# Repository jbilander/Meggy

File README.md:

# Meggy
A 1MB USB-programmable Kickstart ROM board for Amiga computers with a 42-pin ROM socket (A500+, A600). With a small modification also works in machines with a 40-pin ROM socket such as the A500 rev 6A and B2000.

***

<br />

<br />

<br />

<br />

<br />

***

# Bill of Materials — Meggy Rev C

| Ref | Qty | Value | Description | Package | Notes | Mouser |
|-----|-----|-------|-------------|---------|-------|--------|
| U1 | 2 | — | Pin strip 1×21, 2.54mm pitch, 0.4mm square pins | — | <span title="Cut from 1×50 1.27mm pitch strip, remove every other pin to give 2.54mm pitch. Fits Amiga dual-wipe socket better than standard 0.47mm turned pins.">Pin strip info...</span> | [AliExpress example](https://www.aliexpress.com/item/4000979931385.html) |
| U2 | 1 | AT90USB1286-MU | AVR USB microcontroller | QFN-64 | | [556-AT90USB1286-MU](https://www.mouser.com/ProductDetail/556-AT90USB1286-MU) |
| U3 | 1 | M29F160FT55N3E2 | 2MB NOR Flash (top-boot) | TSOP-48 | | [913-M29F160FT55N3E2](https://www.mouser.com/ProductDetail/913-M29F160FT55N3E2) |
| U4 | 1 | 74AHCT1G126GW | Single tristate buffer | SC-70-5 / SOT-353 | <span title="Isolates Gary's /OE signal from the flash chip during USB programming. 10k pull-up on EN keeps buffer enabled by default even with no firmware loaded.">OE isolation...</span> | [771-AHCT1G126GW125](https://www.mouser.com/ProductDetail/771-AHCT1G126GW125) |
| D1, D2 | 2 | CDBU0520 | Schottky diode 0.5A 20V | SOD-523F / 0603 | <span title="Diode-OR between VBUS (USB 5V) and VCC (Amiga 5V). Prevents backfeed between the two supplies. Higher voltage wins.">Power OR...</span> | [750-CDBU0520](https://www.mouser.com/ProductDetail/750-CDBU0520) |
| X1 | 1 | 16 MHz | Crystal oscillator SG5032CCN 16.000000M-HJGA3 | 5×3.2mm SMD | | [732-5032CC16.0HJGA3](https://www.mouser.com/ProductDetail/732-5032CC16.0HJGA3) |
| SW1 | 1 | — | Sunrom Tactile Switch SMD | 3×4×2mm | <span title="Hold HWB button and run --avr-reset to enter DFU bootloader mode for firmware programming.">HWB / DFU entry...</span> | [AliExpress example](https://www.aliexpress.com/item/32855171871.html) |
| J1 | 1 | 10118194-0001LF | Micro USB-B connector, Amphenol FCI, 5-pin | SMD | | [649-10118194-0001LF](https://www.mouser.com/ProductDetail/649-10118194-0001LF) |
| J2 | 1 | MSK12D19 SMD | SMD slide switch, 3-pin, 2.5mm pitch | SMD | <span title="Flash A19 select — open = slot 1 (pull-up), shorted to GND = slot 0. Pins bent to right angle for flush mounting. Alternatively a 3-pin 2.54mm right-angle pin header with external toggle switch.">Flash A19 slot select...</span> | [AliExpress example](https://www.aliexpress.com/item/1005006482584650.html) |
| RN1, RN2 | 2 | 10k | Resistor network 4×10kΩ isolated | 0603×4 (1206) | CAY16-103J4LF | [652-CAY16-103J4LF](https://www.mouser.com/ProductDetail/652-CAY16-103J4LF) |
| R1, R2 | 2 | 22Ω | CR0603-FX-22R0ELF — USB D+/D− series resistors | 0603 | | [652-CR0603FX-22R0ELF](https://www.mouser.com/ProductDetail/652-CR0603FX-22R0ELF) |
| R3 | 1 | 22Ω | CR0603-FX-22R0ELF — Clock series termination | 0603 | | [652-CR0603FX-22R0ELF](https://www.mouser.com/ProductDetail/652-CR0603FX-22R0ELF) |
| R4 | 1 | 100Ω | CR0603-FX-1000ELF — VBUS detection | 0603 | <span title="Series resistor between VBUS_5V and AVR VBUS pin 8 for USB bus voltage detection.">VBUS detect...</span> | [652-CR0603FX-1000ELF](https://www.mouser.com/ProductDetail/652-CR0603FX-1000ELF) |
| R5 | 1 | 10kΩ | CR0603-FX-1002ELF — OE_BUF_EN pull-up | 0603 | <span title="Pull-up to VCC on PE4 (OE_BUF_EN). Keeps the 74AHCT1G126GW buffer enabled by default so Gary controls /OE even with no firmware loaded.">OE_BUF_EN pull-up...</span> | [652-CR0603FX-1002ELF](https://www.mouser.com/ProductDetail/652-CR0603FX-1002ELF) |
| C1 | 1 | 1µF | CL10B105KA8NNND | 0603 | <span title="UCAP filter capacitor on AVR pin 7. Required for the AT90USB1286 internal USB voltage regulator.">UCAP filter...</span> | [187-CL10B105KA8NNND](https://www.mouser.com/ProductDetail/187-CL10B105KA8NNND) |
| C2, C3, C4, C5 | 4 | 100nF | CL10B104KA8NNNC — Bypass decoupling | 0603 | <span title="Bypass decoupling capacitors. Place as close as possible to the VCC pins of U2, U3 and U4.">Bypass decoupling...</span> | [187-CL10B104KA8NNNC](https://www.mouser.com/ProductDetail/187-CL10B104KA8NNNC) |

## Key ICs

**AT90USB1286-MU** — Atmel/Microchip AVR, 128KB flash, native full-speed USB, QFN-64. Runs the Meggy firmware and provides USB bulk transfer for flash programming. DFU bootloader in hardware boot section (no external programmer needed after initial setup).

**M29F160FT55N3E2** — Micron/ST 16Mbit (2MB) NOR flash, top-boot, 55ns, 5V, x16. Stores two 1MB Kickstart image slots selectable via the A19 switch. [Datasheet](https://www.mouser.com/datasheet/3/893/1/M29FxxFT_FB.pdf)

**74AHCT1G126GW** — Single buffer with tristate output (active-high enable). Isolates Gary's /OE signal from the flash chip during USB programming operations. 10k pull-up on EN ensures the buffer is enabled (Amiga in control) by default even with no firmware loaded.

**CDBU0520** — Comchip 0.5A 20V Schottky diode, SOD-523F (0603 footprint). Two used for power OR between VBUS (USB) and VCC (Amiga). Prevents backfeed between the two supplies.

## Power

The board can be powered from either:
- **VBUS** (USB 5V) — when connected to a PC for programming
- **VCC** (Amiga 5V) — when installed in the Amiga

D1 and D2 form a diode-OR, allowing both supplies to coexist safely. The higher voltage wins. Schottky forward drop is approximately 150–200mV at typical operating currents.

***

# Assembly Notes

## Pin Headers (U1)

The two 1×21 pin headers that plug into the Amiga ROM socket are made from standard **1.27 mm pitch pin strips** with every other pin used, giving 21 pins per row at 2.54 mm pitch.

The reason for starting with 1.27 mm strips rather than conventional 2.54 mm strips is pin geometry: 1.27 mm strips have **0.4 mm square pins**, which seat noticeably better in Amiga dual-wipe sockets than the turned (round) pins found on 2.54 mm strips. Turned pins are typically ~0.47 mm in diameter and can spread the socket contacts over time, whereas the slimmer square pins make clean contact without stressing the socket.

### Preparation

Start with two 1.27 mm pitch pin strips, each at least 42 pins long. Using pliers or a similar tool, push every other pin down flush with the top face of the plastic guard — these are the pins that will not be soldered. The result is a strip that alternates between full-length protruding pins and pins that sit flush inside the guard.

### Self-aligning soldering technique

Place both prepared strips on the work surface with the **plastic guard facing down** and the full-length pins pointing upward. Set the Meggy PCB flat on top so that it rests on the two strips — the full-length pins pass up through the PCB holes from below while the board's own weight holds everything in place.

Align both strips as straight as possible along the PCB edges, then **tack one corner of each strip** to hold them in position.

At this stage it is still easy to correct misalignment — reflow a tacked corner with the iron, nudge the strip with your finger, and re-tack. Check that the pins protrude consistently above the PCB along the full length of each strip before proceeding. When both strips are correctly aligned, solder all remaining pins from the top side.

After soldering, the underside of the board looks like this:

### Removing the plastic guard

With all pins soldered, grip the plastic guard firmly and pull it straight down away from the PCB. The guard separates cleanly by hand — the alternating flush pins are retained inside it and come away with it, leaving only the soldered pins.

The finished board has two neat rows of evenly spaced pins with no plastic guard to limit insertion depth, allowing Meggy to seat fully into any socket.

## J2 Slide Switch (MSK12D19) — Bending and Soldering

The MSK12D19 is an SMD slide switch soldered flat on the PCB with its pins bent over and soldered from the top side. To change the Kickstart slot the Amiga needs to be opened. Alternatively J2 can be fitted with a 3-pin 2.54mm right-angle pin header and wired to an external toggle switch mounted somewhere accessible on the Amiga case.

**Steps:**
1. Place the switch into the J2 footprint so the three pins protrude slightly through the top side of the PCB.
2. With your fingers, bend all three pins over flat against the top surface so the switch body ends up level with the board.
3. Apply flux and solder the three pins from the top side with a regular soldering iron.

## AVR Exposed Pad and USB Connector — Soldering Technique

The AT90USB1286-MU QFN-64 has a large exposed thermal pad on the underside that must be soldered to the GND pour for reliable operation. The Micro USB connector also has through-hole anchor pins. Both benefit from using a desoldering station with good thermal mass — a ZD915 or similar works well for this.

**AVR exposed pad:**
1. Apply flux into the PCB via hole that sits directly under the exposed pad.
2. Place the desoldering nozzle against the hole from the underside and feed solder wire into the nozzle, holding for 3–4 seconds. The thermal mass of the station heats the via quickly and the solder wicks up through the hole making solid contact with the exposed pad above.

**USB connector through-hole anchor pins:**
1. Apply flux on both sides of the PCB at each anchor pin hole.
2. Solder from one side — applying flux to the opposite side encourages a clean bleed-through joint, giving a solid mechanical connection.

***

# Windows Setup

Meggy uses two distinct USB personalities:

| Mode | USB ID | When active | Driver needed |
|------|--------|-------------|---------------|
| **DFU bootloader** | 03EB:2FFB | No firmware, or HWB held during power-up | libusb-win32 (via Zadig) |
| **Flash programmer** | 03EB:2044 | Normal firmware operation | WinUSB (via Zadig) |

Both drivers are installed with [Zadig](https://zadig.akeo.ie). The steps below cover the full setup from a fresh Windows machine.

## Prerequisites

- **Arduino IDE 1.8.x** — provides `avrdude.exe` used by `flash.bat` to program the AVR firmware. Tested with Arduino IDE 1.8.16. Newer versions of Arduino IDE (2.x) install avrdude in a different location and may require editing the `AVR_PATH` variable in `build.bat` and `flash.bat`. Download from [arduino.cc](https://www.arduino.cc/en/software).
- **Python 3.x** — required for `meggy_flash.py` (see Step 1 below).

---

## Step 1 — Install Python

Download Python 3.x (64-bit) from [python.org](https://www.python.org/downloads/) and run the installer.

**Important:** tick **"Add python.exe to PATH"** before clicking Install Now.

---

## Step 2 — Install PyUSB

Open a Command Prompt and run:

```
pip install pyusb
```

If you run `meggy_flash.py` before installing PyUSB you will see the reminder message shown below — just run the pip command and try again.

---

## Step 3 — Install libusb-1.0.dll

PyUSB on Windows requires `libusb-1.0.dll` to be present. Download the latest libusb release from [libusb.info](https://libusb.info), open the archive with 7-Zip or similar, and copy `libusb-1.0.dll` from the `VS2015\MS64\dll\` folder into `C:\Windows\System32`.

---

## Step 4 — Install Zadig

Download [Zadig](https://zadig.akeo.ie) (a single portable `.exe`, no installation required) and save it somewhere convenient.

---

## Step 5 — Install the DFU driver (libusb-win32)

This driver is used when Meggy is in DFU bootloader mode for **firmware** programming.

**Put Meggy into DFU mode:**

A freshly soldered board with no firmware loaded will enter DFU mode automatically on power-up — just plug in the USB cable and the device enumerates as **AT90USB128 DFU** without any button press needed.

If firmware is already installed, hold the HWB button and run `python meggy_flash.py --avr-reset` (see the Firmware Programming section below).

Windows will detect a new device. Without the driver it appears as **AT90USB128 DFU** under *Other devices* in Device Manager with a warning icon.

Open Zadig. The device **AT90USB128 DFU** (USB ID `03EB 2FFB`) should appear in the dropdown. Make sure the target driver on the right is set to **libusb-win32**, then click **Install Driver**.

Zadig installs the driver (this takes a few seconds).

When complete, Zadig reports **"The driver was installed successfully."**

Device Manager now shows **AT90USB128 DFU** under *libusb-win32 devices* — no warning icon.

---

## Step 6 — Install the Flash Programmer driver (WinUSB)

This driver is used during normal operation when Meggy presents itself as the **Meggy Flash Programmer** for **NOR flash** programming.

Unplug Meggy and plug it back in without holding HWB so it boots into normal firmware mode. Windows detects it as **Meggy Flash Programmer** under *Other devices*. If you try to install the driver via Windows Update or Device Manager directly, Windows will refuse because the INF lacks a digital signature.

Use Zadig instead. Select **Meggy Flash Programmer** (USB ID `03EB 2044`) from the dropdown and confirm the target driver on the right is **WinUSB**, then click **Install Driver**.

Zadig installs the driver and reports success.

Device Manager now shows **Meggy Flash Programmer** under *Universal Serial Bus devices*.

Both drivers are now in place and setup is complete.

***

# Firmware Programming

The AT90USB1286 ships with a USB DFU bootloader burned into the hardware boot section. This bootloader cannot be erased, so no external programmer is ever required after the chip is soldered.

## Entering DFU Mode

A freshly soldered board with no firmware loaded will enter DFU mode automatically on power-up — just plug in USB and it enumerates as **AT90USB128 DFU** (USB ID `03EB:2FFB`) without any button press needed.

If firmware is already installed:

**Preferred method** (firmware running):
1. Hold the HWB button.
2. Run `python meggy_flash.py --avr-reset`
3. Release HWB once avrdude connects.

The `--avr-reset` command triggers a hardware reset via the PE5→RESET connection, which causes the bootloader to check HWB and enter DFU mode. This is the only way to enter DFU mode when firmware is already running on Rev C.

## Building the Firmware

From the `firmware/` folder, run:

```bat
build.bat
```

This compiles the firmware and produces `meggy_firmware.hex`. LUFA must be cloned into the `firmware/LUFA/` subfolder first:

```bat
cd firmware
git clone https://github.com/abcminiuser/lufa LUFA
```

## Flashing the Firmware (Windows)

From the `firmware/` folder, run:

```bat
flash.bat
```

This calls `avrdude` with the `flip1` programmer protocol targeting the AT90USB1286 DFU bootloader and handles firmware upload and verification automatically. Some harmless warnings about fuse bits not being accessible via FLIP are expected and can be ignored.

After flashing, power cycle the board to return to normal firmware mode:
- **Standalone:** unplug and replug USB.
- **Installed in Amiga:** disconnect USB and Amiga power, then reconnect.

## Flashing the Firmware (Linux / macOS)

Install `dfu-programmer` via your package manager, then:

```sh
dfu-programmer at90usb1286 erase
dfu-programmer at90usb1286 flash meggy_firmware.hex
dfu-programmer at90usb1286 start
```

The `start` command reboots the AVR automatically into firmware mode. Meggy will enumerate as **Meggy Flash Programmer** (USB ID `03EB:2044`), ready for NOR flash programming.

***

# NOR Flash Programming

With the firmware running and the WinUSB driver installed, use `meggy_flash.py` from the `firmware/` folder to read and write the M29F160 NOR flash over USB.

**Important:** set the J2 switch to the desired slot **before** running any programming commands. The physical switch position determines which 1MB half of the flash chip is accessed — the software always programs whichever slot the switch currently selects.

**Power and bus contention note:** the safest way to program Meggy is standalone — removed from the Amiga socket and powered from USB only. This avoids both power and bus contention issues entirely.

Programming while installed in the Amiga with the Amiga powered off would be equally convenient, but unfortunately does not work reliably. The unpowered chips on the motherboard (CPU, Gary, RAM) draw current through their protection diodes from Meggy's bus lines, dragging down the supply voltage during programming and causing timeouts at around 12% through the image.

With the Amiga powered on, programming works reliably in practice, but there is a theoretical bus contention risk: the address and data lines are shared directly between the AVR and the Amiga bus, and the CPU may drive the same lines simultaneously during any bus cycle. The /OE isolation provided by U4 (74AHCT1G126GW) prevents Gary from asserting /OE on the flash, so the flash will not drive data lines in response to Amiga read cycles — if the CPU attempts a ROM read it simply reads floating lines and stalls or crashes harmlessly. The flash being in read mode between programming operations is the safer state; the contention risk is highest during the brief /WE pulse when the AVR actively drives data lines. In practice the contention window is very brief and programming completes without errors, but for critical or repeated programming operations removing the board first is the cleanest approach.

## Quick-start

```sh
# Identify the device and flash chip
python meggy_flash.py --identify

# Write a Kickstart image (set J2 switch to desired slot first)
python meggy_flash.py --write kick31.rom

# Write a Kickstart image with 16-bit byte-swap applied (for unswapped ROM files)
python meggy_flash.py --write kick31.rom --swap

# Read back the current slot for verification
python meggy_flash.py --read-slot readback.bin

# Verify flash contents against a ROM file
python meggy_flash.py --verify kick31.rom

# Erase the current slot
python meggy_flash.py --erase

# Reset the AVR into DFU mode (hold HWB button while executing this command)
python meggy_flash.py --avr-reset
```

***

# Using Meggy in a 40-pin ROM Socket (A500 rev 6A, A2000)

Meggy is designed for the 42-pin ROM socket found in the A500+ and A600. With a small modification it also works in machines with a 40-pin ROM socket such as the A500 rev 6A and A2000, which lack pin 1 (A19) and pin 42 (A20). The following has been tested on an A500 rev 6A.

## Modifications Required

**J2 slot switch — replace MSK12D19 with a pin header:**
On the A500 rev 6A the can oscillator on the motherboard sits directly below where the MSK12D19 slide switch would be, making it impossible to fit. Desolder the MSK12D19 from J2 and replace it with a standard 3-pin 2.54mm right-angle pin header. A standard 2.54mm jumper shunt can then be used to select the slot, and the right-angle header clears the can oscillator without conflict.

**Remove the plastic guards from the pin strips (if not already done):**
Single-wipe sockets have shallower contact depth than dual-wipe sockets. The plastic guard on the pin strips adds height that may prevent Meggy from seating fully into the socket. If you followed the recommended assembly method in the Pin Headers section above the guards will already have been removed as the final step of soldering — no further action is needed. If the guards are still present, grip each one firmly and pull it straight down away from the PCB; it should separate cleanly by hand, bringing the alternating unused pins with it.

**A19 jumper wire:**
The 42-pin socket has pin 1 carrying the CPU A19 signal, which selects which 512KB bank of the Kickstart the CPU is accessing. The 40-pin socket does not have this pin, so Meggy's pin 1 will hang over the edge of the socket with no connection. A short jumper wire must be soldered from Meggy's pin 1 to the A19 signal on the motherboard.

On the A500 rev 6A the A19 signal is conveniently available at solder jumper JP2 on the motherboard, which is only about 1cm from where Meggy's pin 1 overhangs the socket — making it a very short and clean connection. Alternatively A19 can be found at pin 47 of the 68000 CPU (DIP-64 package).

## Compatibility Notes

- Tested and working on A500 rev 6A with Kickstart 3.1.4 (512KB duplicated) and 1MB capitoline image
- The single-wipe socket on the A500 rev 6A gives less firm contact than a dual-wipe socket — replacing it with a good quality dual-wipe socket is recommended for long term reliability
- The 1MB capitoline extended ROM image works correctly — icon.library 45.22 and workbench.library 45.194 load from extended ROM at $E00000 even when booting an older Workbench disk

## Photos

Meggy with plastic guards still on the pin strips:

Plastic guards removed and laid next to the board. Also visible: the 3-pin right-angle header fitted to J2 in place of the MSK12D19, with a standard jumper shunt for slot selection:

Meggy installed in the A500 rev 6A 40-pin socket. Pin 1 hangs over the left edge of the socket with no connection yet. The can oscillator is visible to the left — this is why the MSK12D19 had to be replaced with a pin header. JP2 carrying the A19 signal is visible on the motherboard just to the left of Meggy's overhanging pin 1:

Meggy installed with the A19 jumper wire connected. Yellow test clip leads run from Meggy's overhanging pin 1 to the A19 signal on the 68000 CPU. JP2 on the motherboard — visible just to the left of Meggy — provides a much neater and closer connection point for a permanent wire:

DiagROM V1.2.1 running on the A500 rev 6A — CPU 68000, 1024kB chip RAM confirmed:

Workbench 1.3 (34.34) booting under Kickstart 3.1.4 (46.143) on the A500 rev 6A. icon.library version 45.22 and workbench.library version 45.194 are both loading from the extended ROM at $E00000 — confirming the full 1MB capitoline image works correctly on the A500 rev 6A:

***

# Power Supply Measurements

The diode-OR power circuit was measured with a multimeter to verify correct operation. All measurements taken with Meggy Rev C installed in the Amiga. Click any image for full size.

**USB VBUS and Schottky drop — Amiga off, USB plugged:**

Left to right: **5.103V** raw USB VBUS before D2 — **4.85V** on BOARD_5V after D2 (~250mV Schottky drop) — **0.9mV** on Amiga VCC rail, effectively zero. D1 correctly blocks backfeed from BOARD_5V into the unpowered Amiga.

**Amiga powered on — USB plugged and unplugged:**

Left to right: **5.103V** VBUS before Schottky with Amiga on and USB plugged — **4.888V** on BOARD_5V with Amiga on and USB plugged — **4.885V** on BOARD_5V with Amiga on and USB unplugged. The diode-OR selects the higher of the two supplies; with only Amiga VCC present the board runs stably at 4.885V.

***

# Image Slot Selection (J2)

J2 controls flash address line A19, selecting which of the two 1MB Kickstart image slots is visible to the Amiga at boot. The switch position also determines which slot is programmed when using `meggy_flash.py`.

| J2 position | Flash A19 | Slot | Typical use |
|-------------|-----------|------|-------------|
| Open | High (10k pull-up) | Slot 1 | Second image |
| Shorted to GND | Low | Slot 0 | Primary / default image |

The switch can be either the MSK12D19 SMD slide switch specified in the BOM (pins bent to right-angle for flush mounting) or a 3-pin 2.54 mm right-angle pin header fitted with an external toggle or jumper.

To change Kickstart without opening the Amiga, route a short cable from J2 to a switch mounted in a convenient location on the machine.

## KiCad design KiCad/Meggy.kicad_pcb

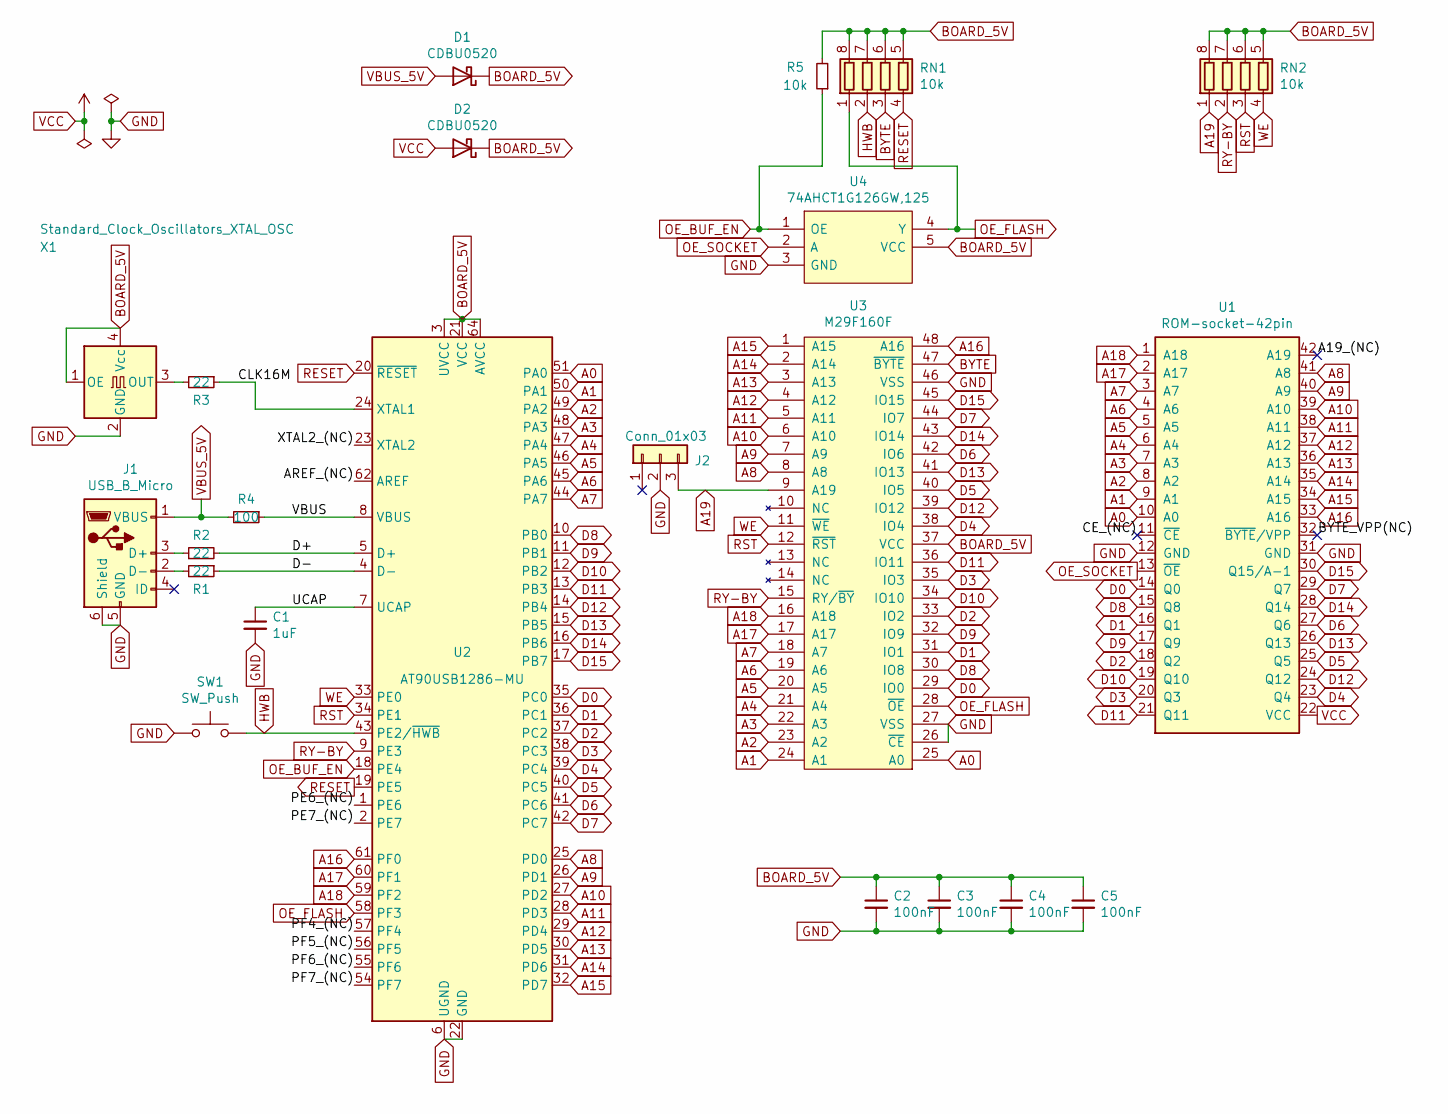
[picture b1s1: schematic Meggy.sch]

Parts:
C1: 1uF; C_0603_1608Metric_Pad1.08x0.95mm_HandSolder
C2, C3, C4, C5: 100nF; C_0603_1608Metric_Pad1.08x0.95mm_HandSolder
D1, D2: CDBU0520; D_0603_1608Metric_Pad_0.975x0.95mm_HandSolder
J1: USB_B_Micro; 101181940001LF
J2: Conn_01x03; PinHeader_1x03_P2.54mm_Vertical
R1, R2: 22; R_0603_1608Metric_Pad0.98x0.95mm_HandSolder
R3: 22; R_0603_1608Metric
R4: 100; R_0603_1608Metric_Pad0.98x0.95mm_HandSolder
R5: 10k; R_0603_1608Metric
RN1, RN2: 10k; RESCAF80P320X160X60-8N
SW1: SW_Push; Sunrom_Tactile_Switch_3x4x2mm_SMD_2-Pin
U1: ROM-socket-42pin; DIP-42_W15.24mm
U2: AT90USB1286-MU; QFN50P900X900X100-65N-D
U3: M29F160F; TSOP-I-48_18.4x12mm_P0.5mm
U4: 74AHCT1G126GW,125; SOT-353_SC-70-5
X1: Standard_Clock_Oscillators_XTAL_OSC; Oscillator_SMD_SeikoEpson_SG8002LB-4Pin_5.0x3.2mm

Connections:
/A19_(NC): U1.42 (A19)
/AREF_(NC): U2.62 (AREF)
/BYTE_VPP(NC): U1.32 (~BYTE~/VPP)
/CE_(NC): U1.11 (~CE)
/CLK16M: R3.1, U2.24 (XTAL1)
/D+: R2.2, U2.5 (D+)
/D-: R1.1, U2.4 (D-)
/PE6_(NC): U2.1 (PE6)
/PE7_(NC): U2.2 (PE7)
/PF4_(NC): U2.57 (PF4)
/PF5_(NC): U2.56 (PF5)
/PF6_(NC): U2.55 (PF6)
/PF7_(NC): U2.54 (PF7)
/UCAP: C1.1, U2.7 (UCAP)
/VBUS: R4.1, U2.8 (VBUS)
/XTAL2_(NC): U2.23 (XTAL2)
A0: U1.10 (A0), U2.51 (PA0), U3.25 (A0)
A1: U1.9 (A1), U2.50 (PA1), U3.24 (A1)
A2: U1.8 (A2), U2.49 (PA2), U3.23 (A2)
A3: U1.7 (A3), U2.48 (PA3), U3.22 (A3)
A4: U1.6 (A4), U2.47 (PA4), U3.21 (A4)
A5: U1.5 (A5), U2.46 (PA5), U3.20 (A5)
A6: U1.4 (A6), U2.45 (PA6), U3.19 (A6)
A7: U1.3 (A7), U2.44 (PA7), U3.18 (A7)
A8: U1.41 (A8), U2.25 (PD0), U3.8 (A8)
A9: U1.40 (A9), U2.26 (PD1), U3.7 (A9)
A10: U1.39 (A10), U2.27 (PD2), U3.6 (A10)
A11: U1.38 (A11), U2.28 (PD3), U3.5 (A11)
A12: U1.37 (A12), U2.29 (PD4), U3.4 (A12)
A13: U1.36 (A13), U2.30 (PD5), U3.3 (A13)
A14: U1.35 (A14), U2.31 (PD6), U3.2 (A14)
A15: U1.34 (A15), U2.32 (PD7), U3.1 (A15)
A16: U1.33 (A16), U2.61 (PF0), U3.48 (A16)
A17: U1.2 (A17), U2.60 (PF1), U3.17 (A17)
A18: U1.1 (A18), U2.59 (PF2), U3.16 (A18)
A19: J2.3, RN2.1 (R1.1), U3.9 (A19)
BOARD_5V: C2.1, C3.1, C4.1, C5.1, D1.1 (K), D2.1 (K), R5.2, RN1.5 (R4.2), RN1.6 (R3.2), RN1.7 (R2.2), RN1.8 (R1.2), RN2.5 (R4.2), RN2.6 (R3.2), RN2.7 (R2.2), RN2.8 (R1.2), U2.3 (UVCC), U2.21 (VCC), U2.52 (VCC), U2.64 (AVCC), U3.37 (VCC), U4.5 (VCC), X1.1 (OE), X1.4 (Vcc)
BYTE: RN1.3 (R3.1), U3.47 (~BYTE)
D0: U1.14 (Q0), U2.35 (PC0), U3.29 (IO0)
D1: U1.16 (Q1), U2.36 (PC1), U3.31 (IO1)
D2: U1.18 (Q2), U2.37 (PC2), U3.33 (IO2)
D3: U1.20 (Q3), U2.38 (PC3), U3.35 (IO3)
D4: U1.23 (Q4), U2.39 (PC4), U3.38 (IO4)
D5: U1.25 (Q5), U2.40 (PC5), U3.40 (IO5)
D6: U1.27 (Q6), U2.41 (PC6), U3.42 (IO6)
D7: U1.29 (Q7), U2.42 (PC7), U3.44 (IO7)
D8: U1.15 (Q8), U2.10 (PB0), U3.30 (IO8)
D9: U1.17 (Q9), U2.11 (PB1), U3.32 (IO9)
D10: U1.19 (Q10), U2.12 (PB2), U3.34 (IO10)
D11: U1.21 (Q11), U2.13 (PB3), U3.36 (IO11)
D12: U1.24 (Q12), U2.14 (PB4), U3.39 (IO12)
D13: U1.26 (Q13), U2.15 (PB5), U3.41 (IO13)
D14: U1.28 (Q14), U2.16 (PB6), U3.43 (IO14)
D15: U1.30 (Q15/A-1), U2.17 (PB7), U3.45 (IO15)
GND: C1.2, C2.2, C3.2, C4.2, C5.2, J1.5 (GND), J1.6 (Shield), J2.2, SW1.1, U1.12 (GND), U1.31 (GND), U2.6 (UGND), U2.22 (GND), U2.53 (GND), U2.63 (GND), U2.65 (GND), U3.26 (~CE), U3.27 (VSS), U3.46 (VSS), U4.3 (GND), X1.2 (GND)
HWB: RN1.2 (R2.1), SW1.2, U2.43 (PE2/~HWB)
unnamed: J1.2 (D-), R1.2
unnamed: J1.3 (D+), R2.1
unnamed: R3.2, X1.3 (OUT)
OE_BUF_EN: R5.1, U2.18 (PE4), U4.1 (OE)
OE_FLASH: RN1.1 (R1.1), U2.58 (PF3), U3.28 (~OE), U4.4 (Y)
OE_SOCKET: U1.13 (~OE), U4.2 (A)
RESET: RN1.4 (R4.1), U2.19 (PE5), U2.20 (~RESET)
RST: RN2.3 (R3.1), U2.34 (PE1), U3.12 (~RST)
RY-BY: RN2.2 (R2.1), U2.9 (PE3), U3.15 (RY/~BY)
VBUS_5V: D1.2 (A), J1.1 (VBUS), R4.2
VCC: D2.2 (A), U1.22 (VCC)
WE: RN2.4 (R4.1), U2.33 (PE0), U3.11 (~WE)

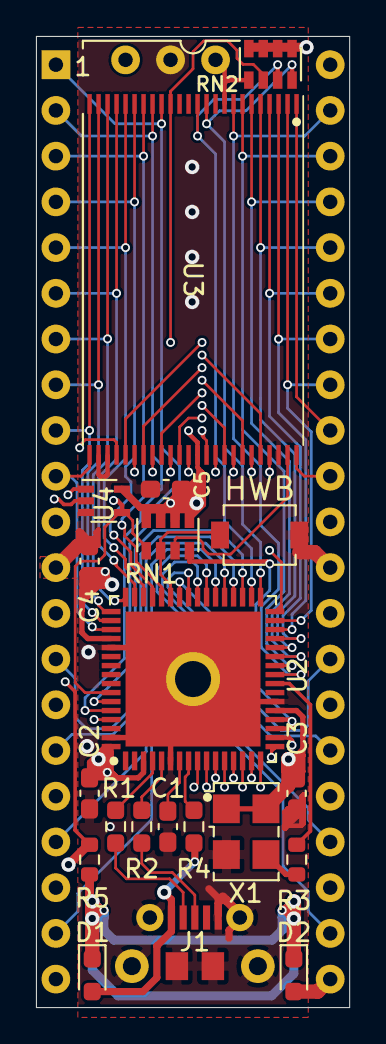
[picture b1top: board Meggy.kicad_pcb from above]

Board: 4 copper layers, 17.4 x 54.0 mm, 22 parts (0 on the bottom side), 57 nets.

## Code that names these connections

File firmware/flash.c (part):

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/* -----------------------------------------------------------------------
 * Pin mapping:
 *
 *   D0-D7   = PC0-PC7
 *   D8-D15  = PB0-PB7
 *   A0-A7   = PA0-PA7
 *   A8-A15  = PD0-PD7
 *   A16     = PF0
 *   A17     = PF1
 *   A18     = PF2
 *   /OE     = PF3
 *   RY/BY   = PE3
 *   /WE     = PE0
 *   /RST    = PE1
 *   HWB     = PE2  (DFU bootloader button, input only)
 *   PE5     = RESET (connected to AVR /RESET pin for software DFU entry)
 *   OE_BUF_EN = PE4 (74AHCT1G126GW enable, 10k pull-up — default enabled)
 *   /CE     = GND  (always asserted)
 *   /BYTE   = VCC  (word mode, 16-bit)
 *
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 * since nothing is connected to those pins.
 * ----------------------------------------------------------------------- */

/* /WE on PE0 */
#define WE_HIGH()     (PORTE |=  (1 << PE0))
#define WE_LOW()      (PORTE &= ~(1 << PE0))

/* /RST on PE1 */
#define RST_HIGH()    (PORTE |=  (1 << PE1))
#define RST_LOW()     (PORTE &= ~(1 << PE1))

/* /OE on PF3 */
#define OE_HIGH()     (PORTF |=  (1 << PF3))
#define OE_LOW()      (PORTF &= ~(1 << PF3))

/* RY/BY on PE3 — high = ready, low = busy */
#define RYBY_READY()  (PINE & (1 << PE3))

/* -----------------------------------------------------------------------
 * Data bus helpers
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 * Address bus helper
 *   PA  = A0-A7
 *   PD  = A8-A15
 *   PF2 = A18, PF1 = A17, PF0 = A16
 *
 * Preserve PF3 (/OE) and PF4-PF7 (unused/JTAG — don't touch).
 * Mask 0xF8 keeps bits [7:3], writes new value into bits [2:0].
 * ----------------------------------------------------------------------- */
static inline void set_address(uint32_t wa)
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{
    DDRA  = 0xFF;           /* A0-A7  outputs */
    DDRD  = 0xFF;           /* A8-A15 outputs */
    /* PF0=A16, PF1=A17, PF2=A18, PF3=/OE — all outputs */
    DDRF  = 0x0F;
    /* /OE starts high (deasserted) — flash_cmd and flash_read_buffer
     * will assert it at the right time */
    PORTF = (1 << PF3);
}

static void flash_cmd(uint32_t word_addr, uint16_t cmd)
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

/* -----------------------------------------------------------------------
 * OE buffer (74AHCT1G126GW) control — PE4 with external 10k pull-up.
 *
 * Pull-up keeps buffer ENABLED by default (Amiga in control of /OE).
 * Driving PE4 low tristates the buffer, giving AVR sole control of /OE.
 *
 * PE4 is connected to the 74AHCT1G126GW enable pin.
 * ----------------------------------------------------------------------- */
void oe_buf_isolate(void)
{
    /* Drive PE4 low — tristate the buffer, isolate Gary from flash /OE */
    DDRE  |=  (1 << PE4);
    PORTE &= ~(1 << PE4);
}

void oe_buf_release(void)
{
    /* Return PE4 to input — external 10k pull-up re-enables the buffer */
    DDRE  &= ~(1 << PE4);
    PORTE &= ~(1 << PE4);
}

void flash_bus_release(void)
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    PORTF = 0x00;

    /* /WE and /RST stay as outputs held high */
    PORTE |= (1 << PE0) | (1 << PE1);  /* /WE=1, /RST=1 */
}

void flash_init(void)
{
    /* Disable SPI — PB0-3 repurposed for D8-D11 */
    SPCR = 0;

    /* Disable ADC — PF0-2 now used as address outputs, not ADC inputs */
    ADCSRA = 0;

    /* ---- Address bus outputs, cleared ---- */
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    /*
     * PORTF:
     *   PF7-PF4 = unused (JTAG pins — leave as inputs, nothing connected)
     *   PF3     = /OE    — output, start high (deasserted)
     *   PF2     = A18    — output, start 0
     *   PF1     = A17    — output, start 0
     *   PF0     = A16    — output, start 0
     *
     * DDRF: set bits [3:0] as outputs, leave [7:4] as inputs (0).
     */
    DDRF  = 0x0F;
    PORTF = (1 << PF3);     /* /OE high, A16-A18 = 0, no pull-ups on PF4-7 */

    /* Set DDRE explicitly — do not rely on reset state.
     * Write PORT before DDR to avoid a brief low glitch on outputs. */
    PORTE = (PORTE & ~((1<<PE4)|(1<<PE5)|(1<<PE6)|(1<<PE7)))
          | (1 << PE0)   /* /WE  high */
          | (1 << PE1);  /* /RST high */
    DDRE  = (1 << PE0) | (1 << PE1);  /* only PE0 and PE1 as outputs */

    /* ---- Data bus: high-Z initially ---- */
    data_bus_input();
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
void flash_hw_reset(void)
{
    /* Hardware reset via /RST pin (PE1) — works from any state.
     * tRP min = 100 ns, tRH min = 100 ns per datasheet.
     * We use a much longer pulse to ensure recovery from
     * post-program/erase status mode. */
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
bool flash_is_ready(void)
{
    return (bool)(PINE & (1 << PE3));
}

uint32_t flash_read_id(void)
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
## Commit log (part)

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2025-09-15 Add LICENSE
2025-09-17 Add KiCad files
2025-09-17 Add USB-Micro footprint for 10118194-0001LF
2025-09-17 Add 3D model of Micro USB connector 10118194-0001LF
2025-09-17 Add Micro USB connector and resistors R1-R3
2025-09-18 Removed the exposed pad on the underside B.cu layer
2025-09-18 Add U3 M29F160F, pin assignment and preliminary routing
2025-09-18 Remove unused symbols
2025-09-19 Add capacitors and a XTAL_OSC plus 22 Ohm resistor for 16MHz clock and more placement and routing
2025-09-20 Add MOSFET DMP2305U-7 to library
2025-09-20 Added Q1 and Q2 MOSFETs, changed footprint on CLK16M resistor and routed RST and WE signals
2025-09-20 Add footprint
2025-09-20 Removed R5,R6 and added D1,D2 changing the 5V Power Protection & ORing Circuit
2025-09-21 Add circuit for controlling Flash-OE signal
2025-09-21 Add 10k pull-up resistor network for RY-BY, WE, RST and A19 signals
2025-09-21 Fix footprint for diode D3 and silkscreen fixes
2025-09-21 Add GND via stitching and some improved routing
2025-09-21 Change 3d model for X1
2025-09-21 Add 3D model
2025-09-21 Add push button for RESET and HWB lines
2025-09-21 Add 3D model for push buttons and fix names on pads not used (NC)
2025-09-22 Moving into 6-layer PCB design
2025-09-22 Re-routing improvements inner signal layer
2025-09-22 Re-routing improvements underside signal layer
2025-09-22 Re-routing improvements top side signal layer
2025-09-23 Add keep out copper pour area for USB pin 4
2025-09-23 Add silkscreen text and OSHW-symbol
2025-09-23 Add outputdirectory out/ for gerbers
2025-09-23 Switched back to 4-layer and did magic routing
2025-09-24 Add screenshot images
2026-03-24 Add source file
2026-03-24 Add build and flash files
2026-03-24 Remove Q3 and D3, replace with 74AHCT1G126GW and route OE_SOCKET_EN from pin PE4
2026-03-27 Optimize footprint hole sizes
2026-03-27 Fix pin assignments JTAG conflict, power OR circuit, OE isolation
    - Replace P-channel MOSFET power OR (Q1/Q2) with Schottky diodes
    - Replace Q3 MOSFET OE isolation with 74AHCT1G126GW tristate buffer (PE4 enable, 10k pull-up)
    - Move A16/A17/A18 from PF5/PF6/PF7 (JTAG conflict) to PF0/PF1/PF2
    - Move RY/BY from PF4 (JTAG conflict) to PE3
2026-03-27 Removed RESET-button
2026-03-28 Add source files
2026-03-28 Update build and flash files
2026-03-28 Add CMD_AVR_RESET (watchdog), OE buffer isolation (PE4/74AHCT1G126GW), auto-reset in flash.bat
    - CMD_AVR_RESET (0x08): ACKs then triggers 15ms watchdog reset, bus/OE released first
    - oe_buf_isolate()/oe_buf_release(): PE4 controls 74AHCT1G126GW tristate during erase/program
    - flash.bat: calls --avr-reset after programming to auto-reboot into new firmware
    - meggy_flash.py: --avr-reset flag added
2026-03-28 Update README with BOM
2026-04-13 Remove --image flag (A19 slot is hardware switch only), fix manufacturer ID 0x0001 recognised as valid Micron code
2026-04-13 Add PE5->RESET for DFU entry, fix flash.bat batch syntax errors
    - CMD_AVR_RESET now drives PE5 low to assert hardware RESET instead of watchdog
    - PE5 (pin 19) bridged to RESET (pin 20) on Rev B PCB, permanent trace in Rev C
    - flash.bat: fix parenthesis escaping causing premature if-block termination
    - flash.bat: remove -D flag, use temp file instead of pipe for reliable exit code
    - flash.bat: add power cycle instructions after successful flash
    - build.bat: update DFU entry instructions to reflect PE5 reset method
2026-04-14 Rev C: connect PE5 (pin 19) to /RESET (pin 20) for software DFU entry via --avr-reset
2026-04-14 Add schematic pdf
2026-04-14 Update screenshots of rev C
2026-04-14 Add images
2026-04-14 Clean up code comments: remove Rev A/B bodge wire references, unused wdt.h include, fix manufacturer ID and PE5 reset description
2026-04-14 Replace SW1 with HWB button in build.bat and flash.bat output messages
2026-04-20 Rename images
2026-04-22 rename file
2026-04-22 Add A500 rev 6A / 40-pin socket compatibility — modifications, installation photos and confirmed working with DiagROM and 1MB capitoline KS 3.1.4
2026-04-22 Add plastic guard orientation tip to pin headers assembly section

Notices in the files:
KiCad/Meggy.kicad_pcb:
Design by J.Bilander (C) 2025,2026
